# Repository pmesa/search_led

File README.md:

# SEARCH LEDs

## You need to install the arduino [IDE](https://www.arduino.cc/en/Guide/Linux)

## You need to install the FastLED and LEDMatrix libraries into your Arduino libraries - [here](https://www.arduino.cc/en/Guide/Libraries) is an example.

## Then...have fun hacking some pretty patterns. All the working code in in the .ino file

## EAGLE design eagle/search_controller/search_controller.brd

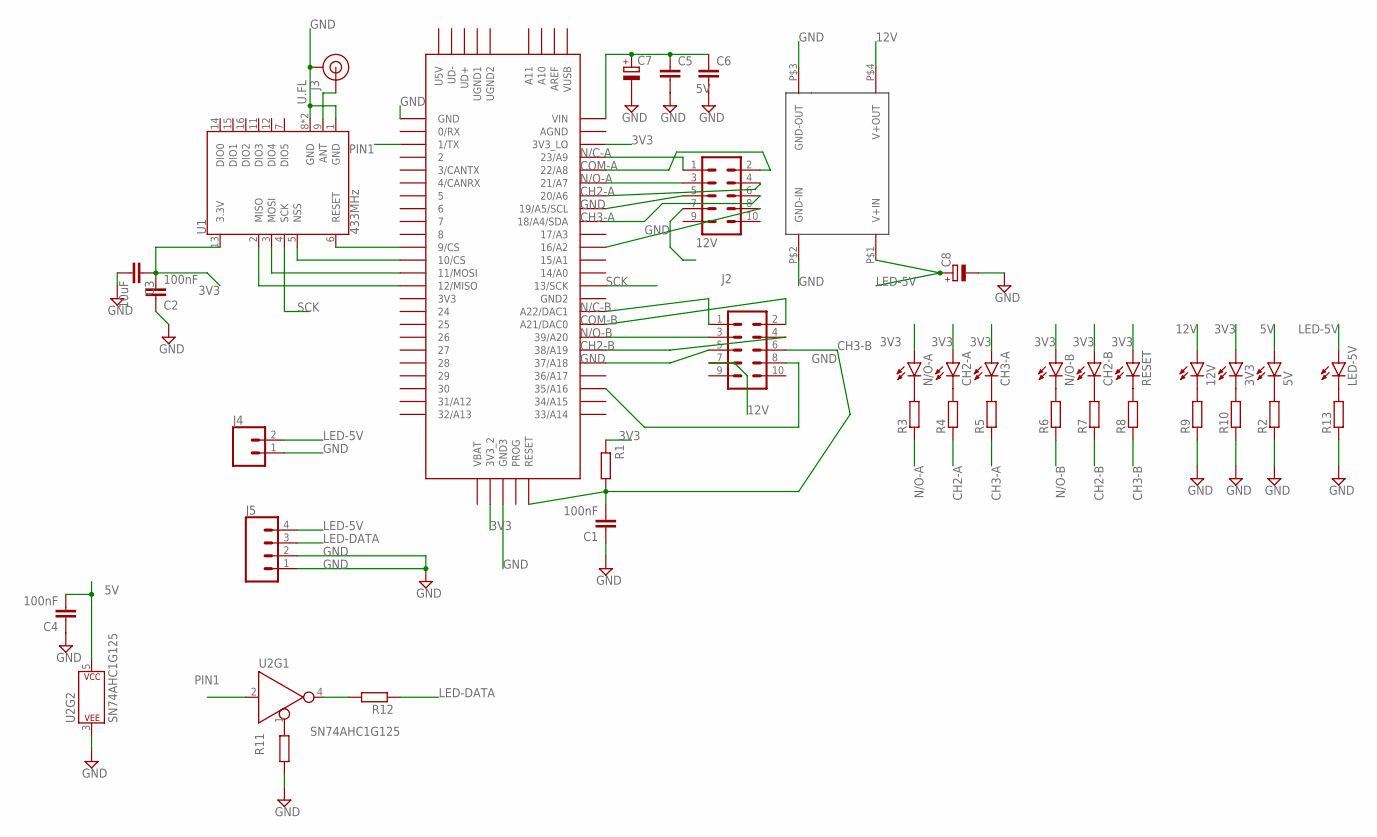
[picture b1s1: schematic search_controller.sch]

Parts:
3V3, 5V, 12V: LEDCHIPLED_0805; CHIPLED_0805
C1, C2, C4: 100nF; C0805
C3: 10uF; C0805
C5, C6: C-EUC0805K; C0805K
C7: CPOL-EUE2,5-6E; E2,5-6E
C8: CPOL-EUE5-8.5; E5-8,5
CH2-A, CH2-B, CH3-A: LEDCHIPLED_0805; CHIPLED_0805
J1, J2: CONN_05X2PTH; 2X5
J3: U.FL
J4: CONN_023.5MM-NO_SILK; SCREWTERMINAL-3.5MM-2-NS
J5: CONN_04; 1X04
LED-5V: LEDCHIPLED_0805; CHIPLED_0805
N/O-A: LEDCHIPLED_0805; CHIPLED_0805
N/O-B: LEDCHIPLED_0805; CHIPLED_0805
R1: R-EU_M0805; M0805
R2, R3, R4, R5, R6, R7, R8, R9, R10, R11, R12, R13: R-EU_R0603; R0603
RESET: LEDCHIPLED_0805; CHIPLED_0805
U1: 433MHz; RFM69HCW-XXXS2
U2: SN74AHC1G125; SOT23-5
U$1: TEENSY_3.5/3.6
U$2: BUCK/BOOST; STANDARDBUCKBOOST

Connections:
3V3: 3V3.A, C2.2, C3.1, CH2-A.A, CH2-B.A, CH3-A.A, N/O-A.A, N/O-B.A, R1.2, RESET.A, U1.13 (3.3V), U$1.3V3_2, U$1.3V3_LO
5V: 5V.A, C4.2, C5.1, C6.1, C7.+, U2.5 (P$V+), U$1.VIN
12V: 12V.A, J1.7, J2.7, U$2.P$4 (V+OUT)
CH2-A: J1.4, R4.1, U$1.20/A6
CH2-B: J2.4, R7.1, U$1.38/A19
CH3-A: J1.6, R5.1, U$1.18/A4/SDA
CH3-B: C1.2, J2.6, R1.1, R8.1, U$1.RESET
COM-A: J1.2, U$1.22/A8
COM-B: J2.2, U$1.21/DAC0 (A21/DAC0)
GND: C1.1, C2.1, C3.2, C4.1, C5.2, C6.2, C7.-, C8.-, J1.5, J1.8, J2.5, J2.8, J3.1 (GND), J3.2 (GND), J4.1, J5.1, J5.2, R2.1, R9.1, R10.1, R11.1, R13.1, U1.1 (GND), U1.8 (GND), U1.10 (GND), U2.3 (P$V-), U$1.16/A2, U$1.19/A5/SCL, U$1.35/A16, U$1.37/A18, U$1.GND, U$1.GND3, U$2.P$2 (GND-IN), U$2.P$3 (GND-OUT)
LED-5V: C8.+, J4.2, J5.4, LED-5V.A, U$2.P$1 (V+IN)
LED-DATA: J5.3, R12.1
unnamed: U1.2 (MISO), U$1.12/MISO
unnamed: U1.3 (MOSI), U$1.11/MOSI
unnamed: U1.5 (NSS), U$1.10/CS
unnamed: J3.FEED (SIGNAL), U1.9 (ANT)
unnamed: U1.6 (RESET), U$1.9/CS
unnamed: N/O-A.C, R3.2
unnamed: CH2-A.C, R4.2
unnamed: CH3-A.C, R5.2
unnamed: N/O-B.C, R6.2
unnamed: CH2-B.C, R7.2
unnamed: R8.2, RESET.C
unnamed: 12V.C, R9.2
unnamed: 3V3.C, R10.2
unnamed: R12.2, U2.4 (Y)
unnamed: LED-5V.C, R13.2
unnamed: 5V.C, R2.2
unnamed: R11.2, U2.1 (!EN)
N/C-A: J1.1, U$1.23/A9
N/C-B: J2.1, U$1.A22/DAC1
N/O-A: J1.3, R3.1, U$1.21/A7
N/O-B: J2.3, R6.1, U$1.39/A20
PIN1: U2.2 (A), U$1.1/TX
SCK: U1.4 (SCK), U$1.13/SCK

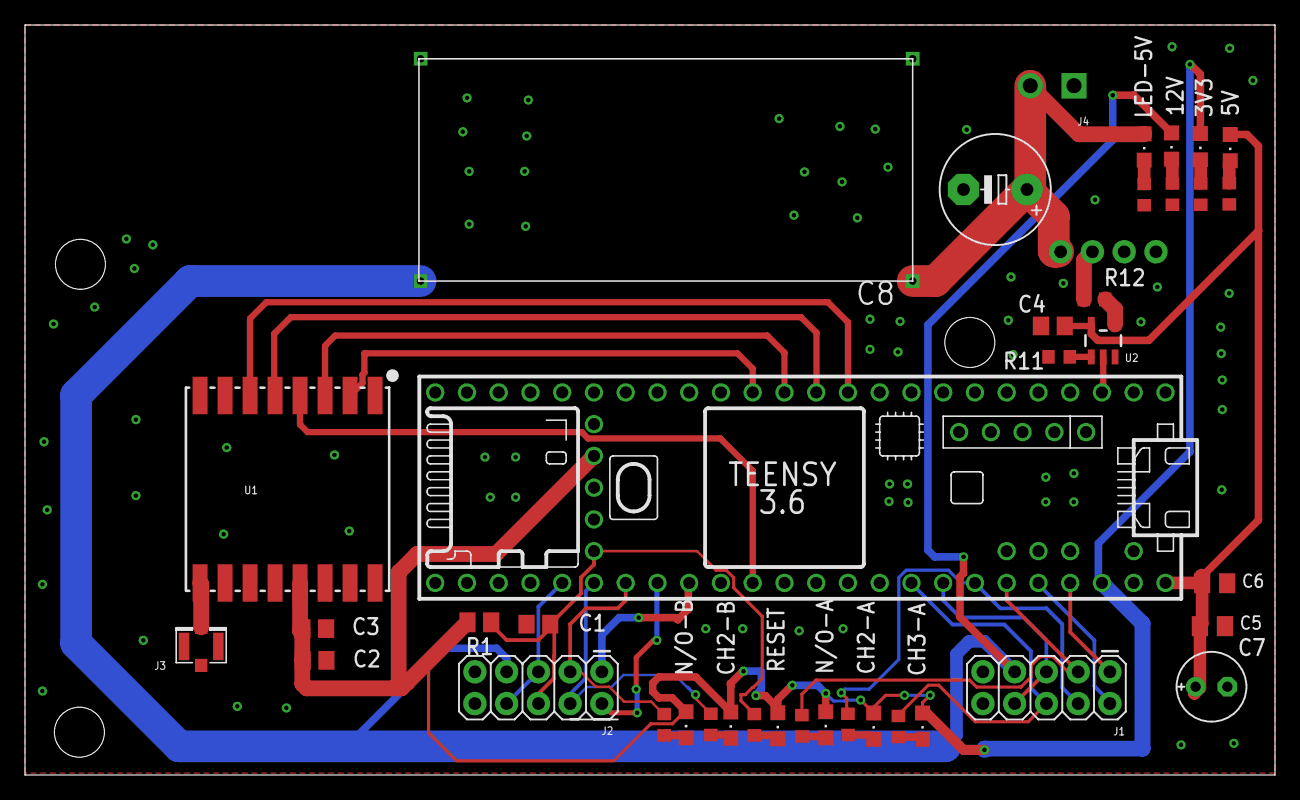
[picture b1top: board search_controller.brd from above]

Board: 2 copper layers, 100.0 x 60.0 mm, 40 parts (1 on the bottom side), 35 nets.

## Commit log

2018-12-11 New File Structure
    fire .ino file
2018-12-18 Exploding circles!
2018-12-18 Added readme
2018-12-20 Rainbow Noise
2018-12-20 Chevron
2018-12-20 Comet
2018-12-20 Inputs
2018-12-20 Scrolling Chevrons
2018-12-20 beautiful changes
2018-12-26 On bridge
2018-12-26 Inputs written untested
2018-12-26 Added switch and some other patterns
2018-12-27 last ,imutes
2018-12-27 Leaving the Bridge Set up
    Can change pattern at any time
    Added comets, circle, and NOISE
    Commeted out PIR
2019-12-08 WIP board defines
2019-12-11 WIP changed the pins - not builing
2019-12-17 Up Down Mode working
    little fragile in terms of the delays for debounce, but up down seems to be working
2019-12-17 Commit to fix lost code
2019-12-17 added eagle files too
2019-12-28 Clean up
2019-12-28 Changed tieDiePattern to be random, and slowed it down
2019-12-28 Changed main mode and brightness
2019-12-28 Add Sprite and paul cleanup
2019-12-29 File clean up and + PIR sensor code restructure
    moved all the functions into seperate ino files
    changed the PIR sensor handling so that it doesn't use the main switch to break out of the loop
2019-12-29 Added nye.ino file
2019-12-29 Added Rain - untested
    A few other little cleanups
2019-12-29 Added nye v1
2019-12-29 Rain
    also changed rect
2019-12-29 Fixed up nye
2020-02-27 Last remaining changes before leaving
    Can't really remember whether this is the final on-bridge version!

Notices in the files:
parts and their libraries:
SparkFun-Connectors: Licensing: Creative Commons ShareAlike 4.0 International - https://creativecommons.org/licenses/by-sa/4.0
